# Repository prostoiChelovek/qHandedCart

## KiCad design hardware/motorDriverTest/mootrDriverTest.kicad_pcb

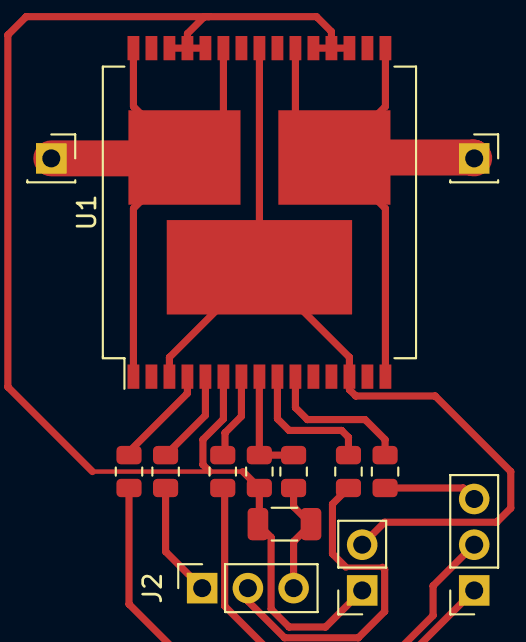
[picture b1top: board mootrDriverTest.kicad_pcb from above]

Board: 2 copper layers, 14 parts (0 on the bottom side), 16 nets.

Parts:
C1: 33nF; C_1206_3216Metric
J1: inputs; PinSocket_1x03_P2.54mm_Vertical
J2: outputs; PinSocket_1x03_P2.54mm_Vertical
J3, J5: Conn_01x01; PinSocket_1x01_P2.54mm_Vertical
J4: power; PinSocket_1x02_P2.54mm_Vertical
R1: 10K; R_0805_2012Metric
R2: 1.5K; R_0805_2012Metric
R3, R4, R5, R6, R7: 1K; R_0805_2012Metric
U1: VNH5019A-E; ST_MultiPowerSO-30

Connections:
+5V: J4.2, U1.3, U1.13, U1.23, U1.31
/back: J1.3, R4.2
/cs: C1.1, J2.3, R1.2
/diag_a: J2.1, R6.2
/diag_b: J2.2, R7.2
/fwd: J1.1, R3.2
/out_a: J3.1, U1.1, U1.25, U1.30, U1.33
/out_b: J5.1, U1.15, U1.16, U1.21, U1.32
/pwm: J1.2, R5.2
GND: C1.2, J4.1, R2.2, U1.6, U1.18, U1.19, U1.20, U1.26, U1.27, U1.28
unnamed: R1.1, R2.1, U1.8
unnamed: R3.1, U1.4
unnamed: R4.1, U1.10
unnamed: R5.1, U1.7
unnamed: R6.1, U1.5
unnamed: R7.1, U1.9

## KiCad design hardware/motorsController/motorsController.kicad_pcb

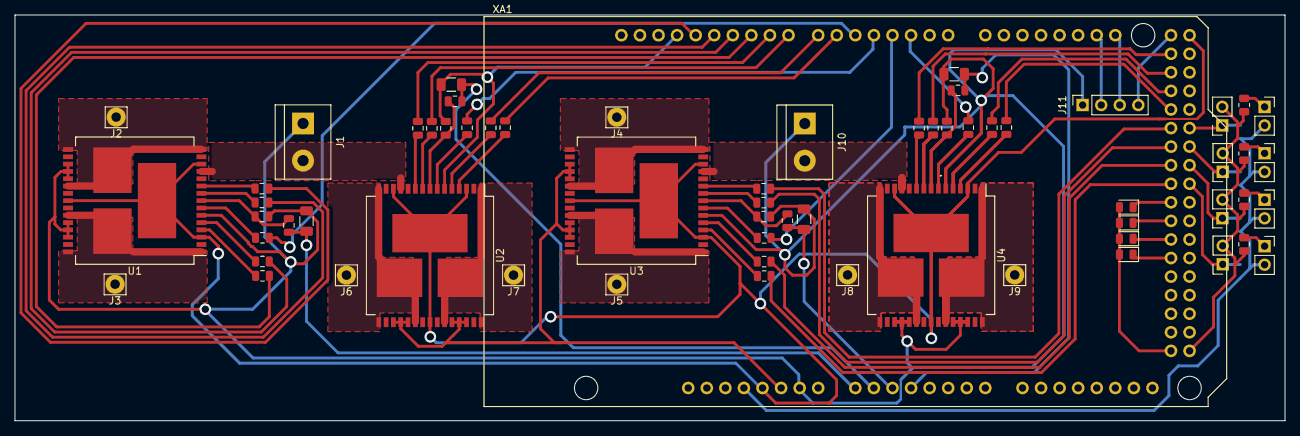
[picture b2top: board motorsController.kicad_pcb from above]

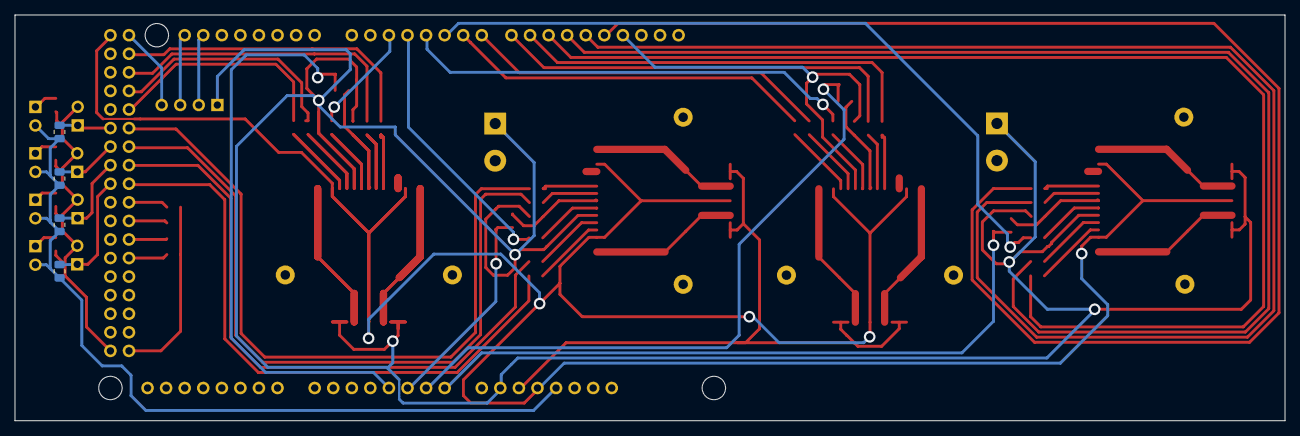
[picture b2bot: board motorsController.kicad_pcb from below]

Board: 2 copper layers, 173.7 x 55.5 mm, 68 parts (4 on the bottom side), 75 nets.

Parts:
C1, C2, C3, C4: 33nF; C_1206_3216Metric
D1, D2, D3, D4: LED; PinSocket_1x02_P2.54mm_Vertical
D5, D6, D7, D8: LED; LED_0805_2012Metric
J1, J10: batery_connector; TerminalBlock_bornier-2_P5.08mm
J2, J3, J4, J5, J6, J7, J8, J9: Screw_Terminal_01x01; Pin_D1.3mm_L11.3mm_W2.8mm_Flat
J11: Conn_01x04; PinSocket_1x04_P2.54mm_Vertical
Q1, Q2, Q3, Q4: Q_Photo_NPN; PinSocket_1x02_P2.54mm_Vertical
R1, R8, R15, R22: 10K; R_0805_2012Metric
R2, R9, R16, R23: 1.5K; R_0805_2012Metric
R3, R4, R5, R6, R7, R10, R11, R12, R13, R14, R17, R18, R19, R20, R21, R24, R25, R26, R27, R28: 1K; R_0805_2012Metric
R29, R30, R31, R32: 50; R_0805_2012Metric
R37, R38, R39, R40: 1k; R_0805_2012Metric
U1, U2, U3, U4: VNH5019A-E; ST_MultiPowerSO-30
XA1: Arduino_Due_Shield

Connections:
+3V3: D1.2, D2.2, D3.2, D4.2, R37.1, R38.1, R39.1, R40.1, XA1.3V3
+5V: J11.4, U1.3, U1.13, U1.23, U1.31, U2.3, U2.13, U2.23, U2.31, U3.3, U3.13, U3.23, U3.31, U4.3, U4.13, U4.23, U4.31, XA1.5V1, XA1.5V3, XA1.5V4
/bat_front+: J1.2, U1.12, U2.12
/bat_rear+: J10.2, U3.12, U4.12
/front_left_encoder: Q2.1, R38.2, XA1.D33
/front_right_encoder: Q1.1, R37.2, XA1.D31
/led_1: D8.1, XA1.D38
/led_2: D7.1, XA1.D40
/led_3: D6.1, XA1.D42
/led_4: D5.1, XA1.D44
/motor_left_front_back: R11.2, XA1.D9
/motor_left_front_cs: C2.1, R8.2, XA1.A1
/motor_left_front_diag_a: R13.2, XA1.D7
/motor_left_front_diag_b: R14.2, XA1.D8
/motor_left_front_fwd: R10.2, XA1.D6
/motor_left_front_pwm: R12.2, XA1.D4
/motor_left_rear_back: R25.2, XA1.D22
/motor_left_rear_cs: C4.1, R22.2, XA1.A3
/motor_left_rear_diag_a: R27.2, XA1.D26
/motor_left_rear_diag_b: R28.2, XA1.D24
/motor_left_rear_fwd: R24.2, XA1.D28
/motor_left_rear_pwm: R26.2, XA1.D2
/motor_right_front_back: R4.2, XA1.D13
/motor_right_front_cs: C1.1, R1.2, XA1.A0
/motor_right_front_diag_a: R6.2, XA1.D11
/motor_right_front_diag_b: R7.2, XA1.D12
/motor_right_front_fwd: R3.2, XA1.D10
/motor_right_front_pwm: R5.2, XA1.D5
/motor_right_rear_back: R18.2, XA1.D30
/motor_right_rear_cs: C3.1, R15.2, XA1.A2
/motor_right_rear_diag_a: R20.2, XA1.D34
/motor_right_rear_diag_b: R21.2, XA1.D32
/motor_right_rear_fwd: R17.2, XA1.D36
/motor_right_rear_pwm: R19.2, XA1.D3
/one_dirver/out_a: J3.1, U1.1, U1.25, U1.30, U1.33
/one_dirver/out_b: J2.1, U1.15, U1.16, U1.21, U1.32
/rear_left_encoder: Q4.1, R40.2, XA1.D37
/rear_right_encoder: Q3.1, R39.2, XA1.D35
/sheet5F8AE5F8/out_a: J7.1, U2.1, U2.25, U2.30, U2.33
/sheet5F8AE5F8/out_b: J6.1, U2.15, U2.16, U2.21, U2.32
/sheet5F8B7955/out_a: J5.1, U3.1, U3.25, U3.30, U3.33
/sheet5F8B7955/out_b: J4.1, U3.15, U3.16, U3.21, U3.32
/sheet5F8B7956/out_a: J9.1, U4.1, U4.25, U4.30, U4.33
/sheet5F8B7956/out_b: J8.1, U4.15, U4.16, U4.21, U4.32
GND: C1.2, C2.2, C3.2, C4.2, D5.2, D6.2, D7.2, D8.2, J1.1, J10.1, J11.1, Q1.2, Q2.2, Q3.2, Q4.2, R2.2, R9.2, R16.2, R23.2, R29.2, R30.2, R31.2, R32.2, U1.6, U1.18, U1.19, U1.20, U1.26, U1.27, U1.28, U2.6, U2.18, U2.19, U2.20, U2.26, U2.27, U2.28, U3.6, U3.18, U3.19, U3.20, U3.26, U3.27, U3.28, U4.6, U4.18, U4.19, U4.20, U4.26, U4.27, U4.28, XA1.GND1, XA1.GND2, XA1.GND3, XA1.GND5, XA1.GND6
unnamed: D1.1, R29.1
unnamed: D2.1, R30.1
unnamed: D3.1, R31.1
unnamed: D4.1, R32.1
unnamed: R1.1, R2.1, U1.8
unnamed: R3.1, U1.4
unnamed: R4.1, U1.10
unnamed: R5.1, U1.7
unnamed: R6.1, U1.5
unnamed: R7.1, U1.9
unnamed: R8.1, R9.1, U2.8
unnamed: R10.1, U2.4
unnamed: R11.1, U2.10
unnamed: R12.1, U2.7
unnamed: R13.1, U2.5
unnamed: R14.1, U2.9
unnamed: R15.1, R16.1, U3.8
unnamed: R17.1, U3.4
unnamed: R18.1, U3.10
unnamed: R19.1, U3.7
unnamed: R20.1, U3.5
unnamed: R21.1, U3.9
unnamed: R22.1, R23.1, U4.8
unnamed: R24.1, U4.4
unnamed: R25.1, U4.10
unnamed: R26.1, U4.7
unnamed: R27.1, U4.5
unnamed: R28.1, U4.9
i2c_scl: J11.2, XA1.D20
i2c_sda: J11.3, XA1.D21

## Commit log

2020-10-01 remove gitattributes
2020-10-01 add schema for motor driver IC
2020-10-08 layout a pcb for the motor driver IC
2020-10-15 reposition motor terminals on both sides of the dirver
2020-10-15 re-layout power connector and components around IC
2020-10-15 layout a schema for three more motor drivers
2020-10-21 replicate layout for three more ICs
2020-10-21 layout and connect power for a pair of drivers
2020-10-21 copy layout to the second pair of drivers
2020-10-21 create a board outline and start routing signal traces
2020-10-21 connect right-rear driver to arduino
2020-10-21 connect left-rear driver to arduino
2020-10-21 reconnect right-rear driver to more conenient pins
2020-10-22 connect left-front driver to arduino
2020-10-22 move left-front driver four pins right
2020-10-22 connect right-front driver to arduino
2020-10-22 connect GNDs
2020-10-22 connect CSs of front motors
2020-10-22 connect 5Vs of drivers
2020-11-12 add an i2c connector
2020-11-19 create a schema for an encoder
2020-11-19 layout filters for an encoder
2020-11-23 connect encoder to arduino
2020-11-26 stage missed sheet with encoder schematics
2020-11-26 add three more encoders
2020-11-26 replicate layout for the rest of encoders
2020-11-26 annotate schematics
2020-11-26 place and connect the rest of encoders
2020-11-26 connect GNDs of encoders' filters to arduino's
2020-11-26 eonnect power for the rest of encoders' leds
2020-11-26 fix tracks for bigger i2c connector
2020-11-26 add a pull-up to encoder's output
2020-11-26 layout pull-up resistors for encoders' outputs
2020-11-26 add indication leds to schematics
2020-11-26 layout indicator leds on a pcb
2020-12-16 create a hypoid gear pinion in blender
2020-12-16 add a short README about gears
2020-12-16 fix a typo in gears' README extension
2020-12-16 stage gears' README with new name
    whoops
2020-12-17 remove a large hole from the gear pinion
2020-12-17 create a hole of a right diameter in the gear pinion
2020-12-17 make a hole in the gear a bit larger
2020-12-17 create a basic shape of the hypoid gear wheel
2020-12-17 add a hole in the hypoid wheel
2020-12-17 export hypoid gears to STL
2020-12-17 fix gears' normals
2020-12-17 mention gears' size deffect in their README
2020-12-17 scale gears in blender
2020-12-17 update gears' STLs
2020-12-18 mesh fixed, 8mm holes created
2020-12-24 add .DS_Store to gitignore
2020-12-24 increase tracks clearance
2020-12-24 increase vias' diameter for one driver
2020-12-24 move encoders' power connectors close to signals
2020-12-24 increase vias' dieamter for front-left driver
2020-12-24 increase vias' dieamter for rear-right driver
2020-12-24 increase vias' dieamter for rear-left driver
2021-02-18 remove RC filter from collector and add resisor before emiter
2021-03-04 layout a pcb for testing a motor driver
2021-09-16 remove old motorsController; create a draft schematic for an H-bridge
2021-09-30 add a test program for PID regulator
2021-09-30 fix linebreaks format
2021-10-07 сcreate a file for the gyro test
2021-10-07 add a library for IRS2453DSPBF
2021-10-21 add a test script for visualization of travelled path
    created not by me
2021-10-25 create some basic classes
    WIP
2021-10-26 implement string conversion for Line
2021-10-26 properly implement Path iteration
2021-10-26 add python stuff to gitignore
2021-10-26 move the test programs into one separate dir
2021-10-26 move path-related stuff to a submodule
2021-10-26 create a module init file for Path
2021-10-26 make Point iteratable and implement custom equality check
2021-10-26 create a test for Point
2021-10-26 make Line iteratable and implement a custom equality check
2021-10-26 implement subtraction for Point and Line
2021-10-26 fix Line slope calculation
2021-10-26 create tests for Line
2021-10-26 create tests for Path
2021-10-26 create a base class for accelerometers
2021-10-26 create a base class for motors
2021-10-26 create a class for chassis and implement some basic functionality
2021-10-26 create a helper class for simultaneous control of several motors
2021-10-26 refactor the ChassisMotors class to return SynchronizedMotors
2021-10-26 refactor Chassis to utilize the functionality of SynchronizedMotors
2021-10-26 describe a basic top-level structure of the software
2021-10-26 rearrange the software graph and detail it a little further
2021-10-26 highlite low-level hardware drivers on the graph
2021-10-26 reflect the odometry module on the graph
2021-10-26 show all four motors on the graph
2021-10-26 Revert "show all four motors on the graph"
    This reverts commit 93dbfc9d980187f06fc8438962d1496de19e6ea4.
2021-10-26 remove redudant module on the graph
2021-10-26 fix arrows' directions and rearrange the graph once again
2021-10-26 place modules at proper ranks on the graph
2021-10-26 remove the odomtery module from the graph
2021-10-30 create a module for hardware drivers and merge it with Sensors
2021-10-30 create a submodule for base classes of drivers
2021-10-30 create a base class for encoders
2021-10-30 change logic of Drivers' __init__
2021-10-30 introduce the odometry module to the graph
    again
2021-10-30 place the wheel module on a level bellow odometry providers
2021-10-30 move the 'Motor' base class to drivers
2021-10-30 create a base class for regulators
2021-10-30 refactor the Pid regulator to implement the 'Regulator' abstract class
2021-10-30 rename the Regulator's file to match the naming convention
2021-10-30 replace the 'numbers.Real' type hint with bare 'float' in Regulator
2021-10-30 add a getter for Motor's current speed
2021-10-30 create a basic implementation of the Wheel controller
2021-10-30 implement a 'stop' method for the Wheel
2021-10-30 replace an abstraction for syncing Motors with the one for Wheels
2021-10-30 update 'Chassis' to operate on Wheels instead of Motors
2021-10-30 create a base class for odometry providers
2021-10-30 extract the ChassisWheels class to a separate file
2021-10-30 create a dummy wheel odometry implementation
2021-10-30 create a dummy accelerometer odometry implementation
2021-10-30 create a dummy implementation of odometry combinator
2021-10-30 clean up the draft version of motorsController schematics
2021-10-31 create a second draft revision of the motorsController's schematic
2021-10-31 add odometry to the Chassis class
2021-10-31 implement the 'set_target' method for the Pid Regulator
    whoops, forgot about it
2021-10-31 move the parameters of the Pid regulator to the Coqpit dataclass
2021-10-31 add a basic config for Chassis
2021-10-31 get rid of Coqpit as it will be replaced with omegaconf
    coqpit does not work with __future__.annotations
    and omegaconf is just better
2021-10-31 create a base class for configurable modules
2021-10-31 evaluate the fields iterator inplace and fix naming of private fields
    map() that was used for constructing the fields' list involves recursion
    it caused some strange behaviour, because map() returns an iterator,
    and iterators are lazy-evaluated
2021-10-31 remove default values for fields of Config dataclasses
    coz i dont wanna deal with the 'non-default argument follows default argument'
    nonsense right now
2021-10-31 make Chassis and its dependencies Configurable
2021-10-31 add Chassis to the __init__ file
2021-11-11 move wheel-related stuff to a separate module from Chassis
2021-11-11 add a property to get time_delta in seconds
2021-11-11 create a wrapper around encoder to get the real linear speed
2021-11-11 create a wrapper around a Motor to allow setting speed in real units
2021-11-11 make the Wheel class use wrappers around Encoder and Motor
    mainly, it fixes unit dimensions in calculations,
    so that they actually make sense
2021-11-12 add Motor direction control and stopping to set_speed of WheelMotor
2021-11-12 make the WheelMotor's speed getter return saved value, not calculated
2021-11-12 create an alias for the 'm/s' unit and replace explicit decls of it
2021-11-12 implement forward and inverse kinematics
2021-11-12 remove the 'stop' method from the Wheel as it's redundant now
2021-11-12 update the SynchronizedWheels class to math the signature of Wheel
2021-11-12 remove redundant methods from Chassis and update speed type hints
2021-11-12 add properties for getting actuall speed to Wheel and SynchronizedWheels
2021-11-12 implement some arithmetic operations for the Velocity dataclass
2021-11-12 implement closed loop velocity control for Chassis
2021-11-12 remove unnecessary stuff from the Chassis class
2021-11-12 move the kinematics module out from Chassis to parent
2021-11-12 add a getter for velocity to the interface of Odometry
2021-11-12 make the Chassis' velocity control loop get actual val from odometry
2021-11-12 remove the 'z' component from structs, as it's redundant for our case
2021-11-12 annotate the coordinates of Point as Unum units
2021-11-12 replace the duplicating struct 'Translation' with 'Point' for Position
2021-11-13 add a method for calculating line angle with the X axis
2021-11-13 remove redundant axis of rotation for Position
2021-11-13 add a getter for chassis' velocity
2021-11-13 separate regulators for linear and angular velocity of Chassis
2021-11-13 implement a SteeringController
2021-11-13 create a helper class for managing stages of the steering process
2021-11-13 implement special handling of the CourseEntering stage
2021-11-13 promote the SteeringStages class to PositionController
2021-11-13 implement a method for calculating Line length
